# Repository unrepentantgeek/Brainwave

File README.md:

Description
===========
Brainwave is a low cost controller for Reprap 3D printers derived from the well known Sanguinololu. The primary design goal was lower cost, achieved by providing only the minimum required components for a single extruder printer.  It can be used to drive a cartesian or delta style printer.

Features:
- Small footprint: only 60mm x 79mm!
- 12V power input
- Micro USB connector
- All connectors at edge of board, vertical or right-angle connectors will fit..
- Atmel AT90USB646 microcontroller w/ USB bootloader
- 1, 2, 16 or 32x microstepping @ up to 800mA
- Dual Z-axis connectors
- Optional per channel current attenuation
- Heated bed support with separate power input (up to 24V @ 15A)
- Integrated heater/thermistor/stepper connector for E channel
- Fan control

Instructions
============
1. Build, buy or borrow a Brainwave
2. Install Arduino 1.0.2
3. install the brainwave arduino hardware bundle from
   [github.com/unrepentantgeek/brainwave-arduino](http://github.com/unrepentantgeek/brainwave-arduino)
   into the Arduino hardware directory.
4. Get Marlin. I am maintaining a branch of Marlin that will compile for
   brainwave at [github.com/unrepentantgeek/Marlin](http://github.com/unrepentantgeek/Marlin/tree/brainwave)
   Marlin HEAD has support, but it doesn't always compile cleanly for this
   board.

Hardware configuration
----------------------
1. Set micro-stepping selector jumpers (D1, D2) per channel.  Short both for 32x
   microstepping.  See table on back of board for other configurations.
   <b>Default: single-step.</b>
2. Set stepper current reference voltages.  I = V / 2.55
   <b>Default: 1V == 400mA.</b>

Software configuration
----------------------

Open Arduino, find the Marlin directory and open Marlin.ino. Select 'Brainwave'
from the Board menu. Find the Configuration.h file and change
DEFAULT_AXIS_STEPS_PER_UNIT to suit your printer (remember, 32x microsteps!)
Power on the Brainwave and connect the USB cable (note: the brainwave will not
power up off USB, you need the 12V supply.) Hold down the PROGRAM button and
press RESET, the STATUS led should pulse. Press the Upload button in Arduino.
After a reset the brainwave will show up as a CDC ACM serial device
(/dev/ttyACM[0..9] on Linux) and be ready to accept commands.

Brandon Bowman wrote up an excellent guide for getting the board working under
Windows and MacOS:
[fabbersuw.blogspot.com/2012/12/if-your-brainwaves-got-no-brains-or.html](http://fabbersuw.blogspot.com/2012/12/if-your-brainwaves-got-no-brains-or.html)

Known issues
------------
- It may take a couple of presses of the RESET button to get the firmware to
  come up after flashing.
- You may need a thermistor or similar 100k resistance present across the bed
  and extruder thermistor inputs. Otherwise Marlin may go into a deathloop and
  you'll never even see a serial device. Even if it doesn't fall on it's face it
  will only sit and complain about too high temp.
- Marlin may lose/gain steps on the X axis.  If so swap X and E to limit the
  impact.  This has not been observed with Sprinter.  The issue is being
  investigated.

Special thanks
--------------
Julie Atwood
Matt Westervelt
Frederik Hubinette
Silas Snider
Johann Rocholl
JP Sugarbroad
Austin Appleby
Richard DeLeon
Plamena Milusheva
Mark Ganter
Brandon Bowman

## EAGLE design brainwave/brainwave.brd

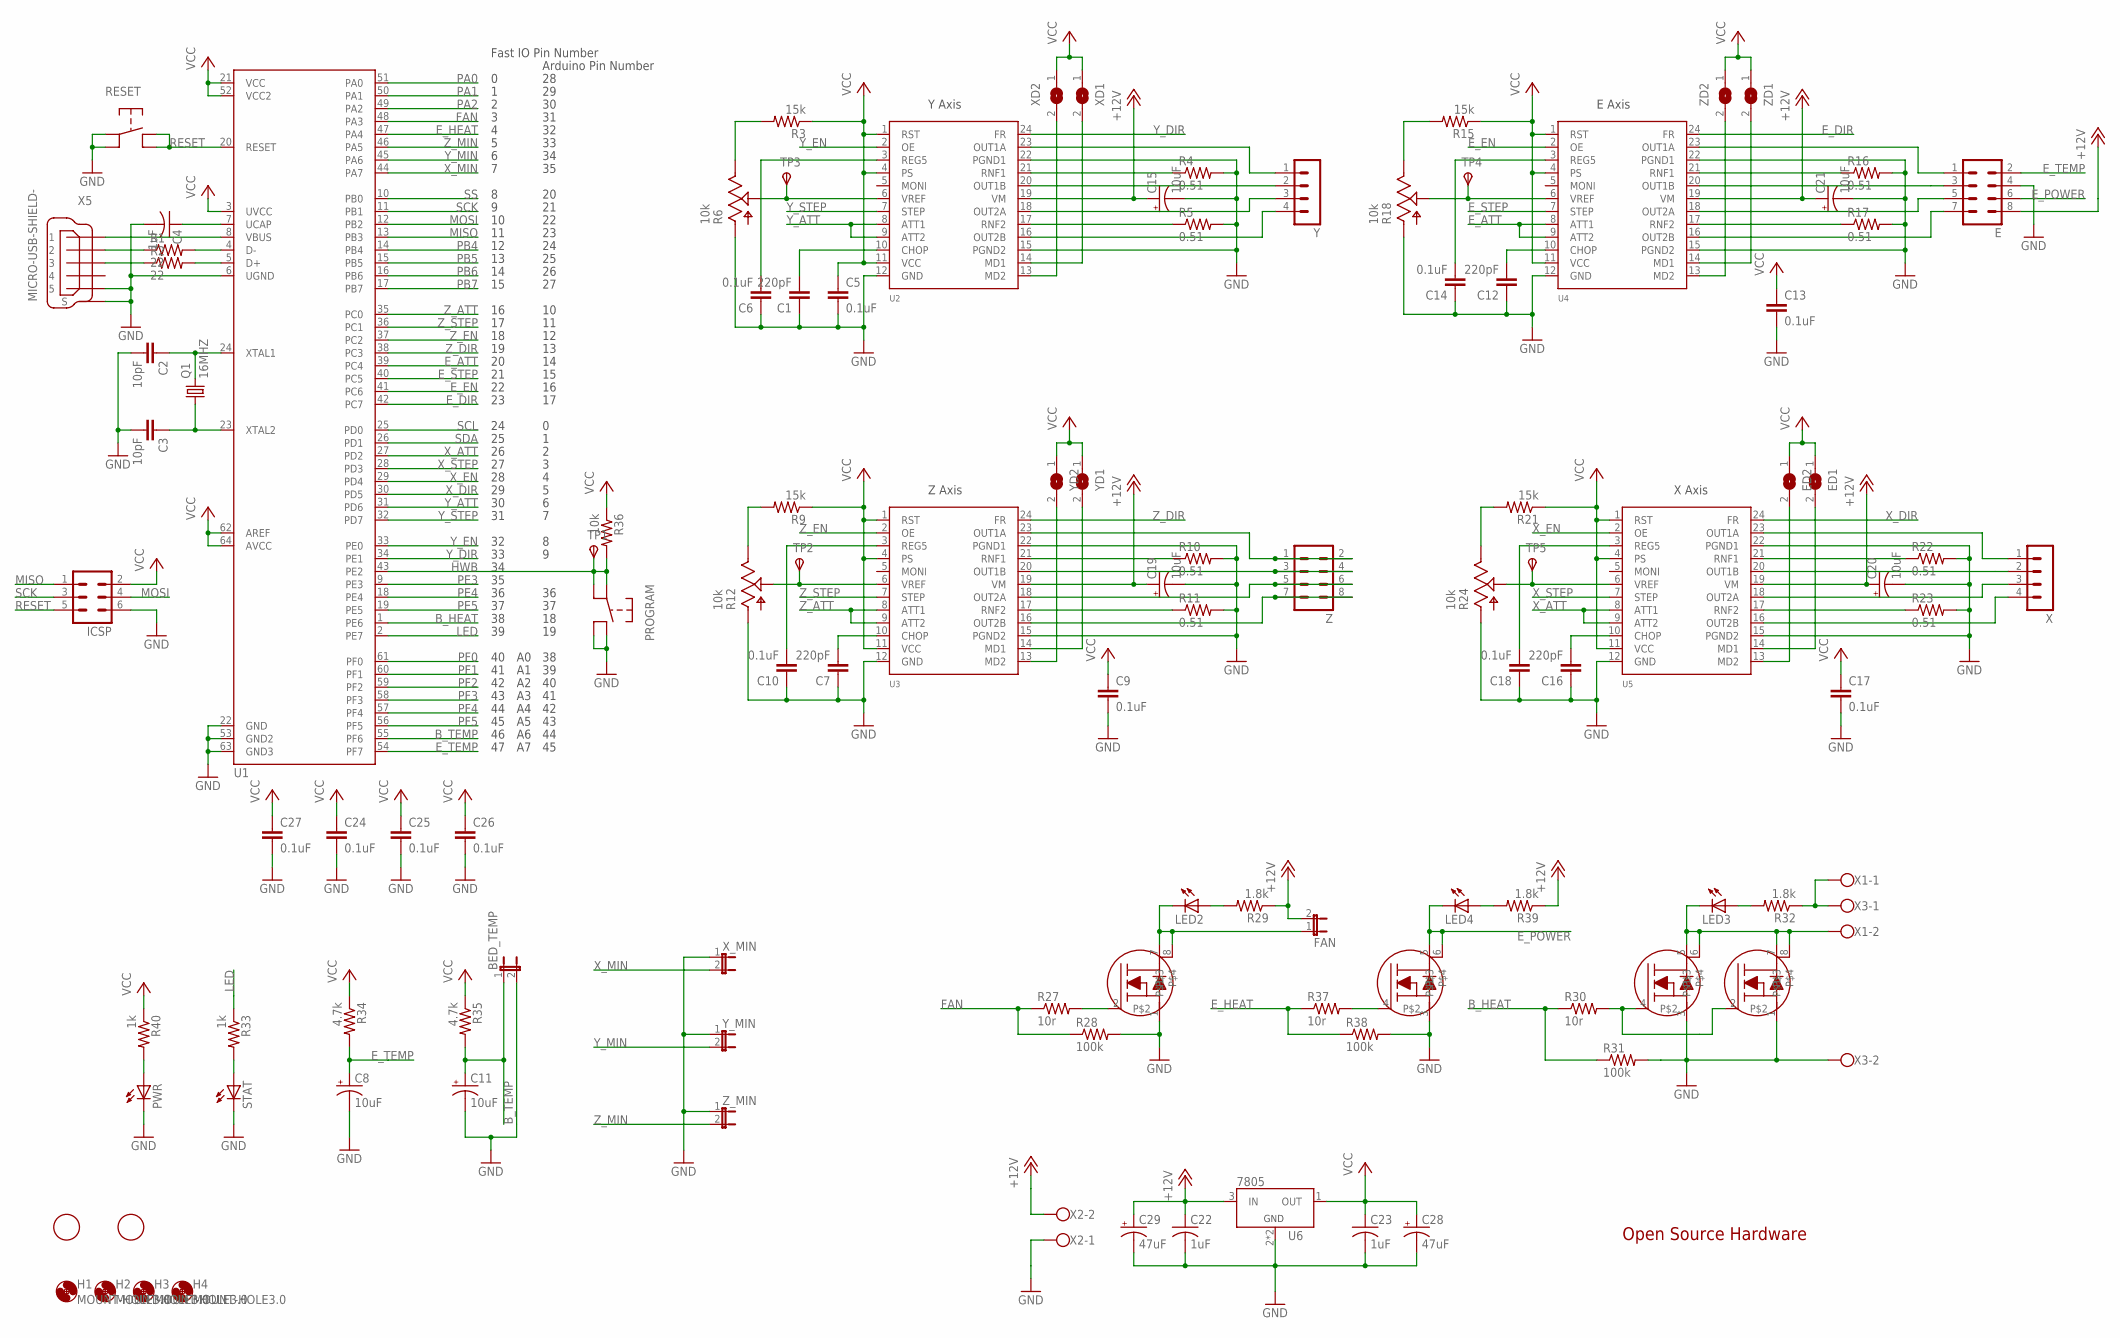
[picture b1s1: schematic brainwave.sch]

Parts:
BED_TEMP: JP1E; JP1
C1, C7, C12, C16: 220pF; C0603
C2, C3: 10pF; C0603
C4, C22, C23: 1uF; C0603
C5, C6, C9, C10, C13, C14, C17, C18, C24, C25, C26, C27: 0.1uF; C0603
C8, C11, C15, C19, C20, C21: 10uF; 153CLV-0505
C28, C29: 47uF; 153CLV-0605
E: MA04-2
ED1, ED2: SJ
FAN: JP1E; JP1
H1, H2, H3, H4: MOUNT-HOLE3.0; 3,0
ICSP: MA03-2
LED2, LED3, LED4: LEDCHIPLED_0805; CHIPLED_0805
PROGRAM: PTS645SMT; PTS645-SMTR
PWR: LEDCHIPLED_0805; CHIPLED_0805
Q1: 16MHZ; CSM-3X
R1, R2: 22; R0603
R3, R9, R15, R21: 15k; R0603
R4, R5, R10, R11, R16, R17, R22, R23: 0.51; R2512
R6, R12, R18, R24: 10k; PVZ3A
R27, R30, R37: 10r; R0603
R28, R31, R38: 100k; R0603
R29, R32, R39: 1.8k; R0603
R33, R40: 1k; R0603
R34, R35: 4.7k; R0603
R36: 10k; R0603
RESET: PTS645SMT; PTS645-SMTR
STAT: LEDCHIPLED_0805; CHIPLED_0805
TP1, TP2, TP3, TP4, TP5: TPSTP08R; TP08R
U1: AT90USB64/128; TQFP64
U2, U3, U4, U5: LV8713T; TSSOP24
U6: 7805; SOT89
U7, U8: IRF8313PBF; SO8
U$1, U$2: FIDUCIAL; FIDUCIAL_1MM
X: MA04-1
X1, X3: W237-102; MPN 237-102
X2: W237-102
X5: MICRO-USB-SHIELD-; 10118192-0001LF
XD1, XD2: SJ
X_MIN: JP1E; JP1
Y: MA04-1
YD1, YD2: SJ
Y_MIN: JP1E; JP1
Z: MA04-2
ZD1, ZD2: SJ
Z_MIN: JP1E; JP1

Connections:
+12V: C15.+, C19.+, C20.+, C21.+, C22.1, C29.+, E.8, FAN.2, R29.1, R39.1, U2.19 (VM), U3.19 (VM), U4.19 (VM), U5.19 (VM), U6.3 (IN), X2.2
BED_POWER: R32.1, X1.1, X3.1
B_HEAT: R30.1, R31.1, U1.1 (PE6)
B_TEMP: BED_TEMP.1, C11.+, R35.2, U1.55 (PF6)
E_ATT: U1.39 (PC4), U4.8 (ATT1), U4.9 (ATT2)
E_DIR: U1.42 (PC7), U4.24 (FR)
E_EN: U1.41 (PC6), U4.2 (OE)
E_HEAT: R37.1, R38.1, U1.47 (PA4)
E_POWER: E.6, LED4.C, U7.5, U7.6
E_STEP: U1.40 (PC5), U4.7 (STEP)
E_TEMP: C8.+, E.2, R34.2, U1.54 (PF7)
FAN: R27.1, R28.1, U1.48 (PA3)
GND: BED_TEMP.2, C1.1, C2.2, C3.2, C4.2, C5.2, C6.1, C7.1, C8.-, C9.2, C10.1, C11.-, C12.1, C13.2, C14.1, C15.-, C16.1, C17.2, C18.1, C19.-, C20.-, C21.-, C22.2, C23.2, C24.2, C25.2, C26.2, C27.2, C28.-, C29.-, E.4, ICSP.6, PROGRAM.P$3, PROGRAM.P$4, PWR.C, R4.2, R5.2, R6.P$1, R10.2, R11.2, R12.P$1, R16.2, R17.2, R18.P$1, R22.2, R23.2, R24.P$1, R28.2, R31.2, R38.2, RESET.P$1, RESET.P$2, STAT.C, U1.6 (UGND), U1.22 (GND), U1.53 (GND2), U1.63 (GND3), U2.12 (GND), U2.15 (PGND2), U2.22 (PGND1), U3.12 (GND), U3.15 (PGND2), U3.22 (PGND1), U4.12 (GND), U4.15 (PGND2), U4.22 (PGND1), U5.12 (GND), U5.15 (PGND2), U5.22 (PGND1), U6.2 (GND), U6.2@1 (GND), U7.1, U7.3, U8.1, U8.3, X2.1, X3.2, X5.5, X5.M1 (S), X5.M2 (S), X5.M3 (S), X5.M4 (S), X5.M5 (S), X5.M6 (S), X_MIN.1, Y_MIN.1, Z_MIN.1
HWB: PROGRAM.P$1, PROGRAM.P$2, R36.2, TP1.TP, U1.43 (PE2)
LED: R33.1, U1.2 (PE7)
MISO: ICSP.1, U1.13 (PB3)
MOSI: ICSP.4, U1.12 (PB2)
unnamed: U1.8 (VBUS), X5.1
unnamed: R1.1, X5.2
unnamed: R2.1, X5.3
unnamed: U3.20 (OUT1B), Z.3, Z.4
unnamed: C4.1, U1.7 (UCAP)
unnamed: C2.1, Q1.2, U1.24 (XTAL1)
unnamed: C3.1, Q1.1, U1.23 (XTAL2)
unnamed: R6.P$2, TP3.TP, U2.6 (VREF)
unnamed: R4.1, U2.21 (RNF1)
unnamed: R5.1, U2.17 (RNF2)
unnamed: U2.16 (OUT2B), Y.4
unnamed: U2.18 (OUT2A), Y.3
unnamed: U2.20 (OUT1B), Y.2
unnamed: U2.23 (OUT1A), Y.1
unnamed: C1.2, U2.10 (CHOP)
unnamed: C6.2, U2.3 (REG5)
unnamed: R3.2, R6.P$3
unnamed: U2.13 (MD2), XD2.2
unnamed: U2.14 (MD1), XD1.2
unnamed: R30.2, U8.2, U8.4
unnamed: R10.1, U3.21 (RNF1)
unnamed: R11.1, U3.17 (RNF2)
unnamed: U3.16 (OUT2B), Z.7, Z.8
unnamed: U3.18 (OUT2A), Z.5, Z.6
unnamed: U3.23 (OUT1A), Z.1, Z.2
unnamed: C7.2, U3.10 (CHOP)
unnamed: C10.2, U3.3 (REG5)
unnamed: R12.P$2, TP2.TP, U3.6 (VREF)
unnamed: R9.2, R12.P$3
unnamed: U3.13 (MD2), YD2.2
unnamed: U3.14 (MD1), YD1.2
unnamed: R33.2, STAT.A
unnamed: R37.2, U7.4
unnamed: LED4.A, R39.2
unnamed: PWR.A, R40.2
unnamed: R16.1, U4.21 (RNF1)
unnamed: R17.1, U4.17 (RNF2)
unnamed: E.7, U4.16 (OUT2B)
unnamed: E.5, U4.18 (OUT2A)
unnamed: E.3, U4.20 (OUT1B)
unnamed: E.1, U4.23 (OUT1A)
unnamed: C12.2, U4.10 (CHOP)
unnamed: C14.2, U4.3 (REG5)
unnamed: R18.P$2, TP4.TP, U4.6 (VREF)
unnamed: R15.2, R18.P$3
unnamed: U4.13 (MD2), ZD2.2
unnamed: U4.14 (MD1), ZD1.2
unnamed: R22.1, U5.21 (RNF1)
unnamed: R23.1, U5.17 (RNF2)
unnamed: U5.16 (OUT2B), X.4
unnamed: U5.18 (OUT2A), X.3
unnamed: U5.20 (OUT1B), X.2
unnamed: U5.23 (OUT1A), X.1
unnamed: C16.2, U5.10 (CHOP)
unnamed: C18.2, U5.3 (REG5)
unnamed: R24.P$2, TP5.TP, U5.6 (VREF)
unnamed: R21.2, R24.P$3
unnamed: ED2.2, U5.13 (MD2)
unnamed: ED1.2, U5.14 (MD1)
unnamed: R27.2, U7.2
unnamed: LED2.A, R29.2
unnamed: FAN.1, LED2.C, U7.7, U7.8
unnamed: LED3.C, U8.5, U8.6, U8.7, U8.8, X1.2
unnamed: LED3.A, R32.2
PA0: U1.51 (PA0)
PA1: U1.50 (PA1)
PA2: U1.49 (PA2)
PB4: U1.14 (PB4)
PB5: U1.15 (PB5)
PB6: U1.16 (PB6)
PB7: U1.17 (PB7)
PE3: U1.9 (PE3)
PE4: U1.18 (PE4)
PE5: U1.19 (PE5)
PF0: U1.61 (PF0)
PF1: U1.60 (PF1)
PF2: U1.59 (PF2)
PF3: U1.58 (PF3)
PF4: U1.57 (PF4)
PF5: U1.56 (PF5)
RESET: ICSP.5, RESET.P$3, RESET.P$4, U1.20 (RESET)
SCK: ICSP.3, U1.11 (PB1)
SCL: U1.25 (PD0)
SDA: U1.26 (PD1)
SS: U1.10 (PB0)
USB1_N: R1.2, U1.4 (D-)
USB1_P: R2.2, U1.5 (D+)
VCC: C5.1, C9.1, C13.1, C17.1, C23.1, C24.1, C25.1, C26.1, C27.1, C28.+, ED1.1, ED2.1, ICSP.2, R3.1, R9.1, R15.1, R21.1, R34.1, R35.1, R36.1, R40.1, U1.3 (UVCC), U1.21 (VCC), U1.52 (VCC2), U1.62 (AREF), U1.64 (AVCC), U2.1 (RST), U2.4 (PS), U2.11 (VCC), U3.1 (RST), U3.4 (PS), U3.11 (VCC), U4.1 (RST), U4.4 (PS), U4.11 (VCC), U5.1 (RST), U5.4 (PS), U5.11 (VCC), U6.1 (OUT), XD1.1, XD2.1, YD1.1, YD2.1, ZD1.1, ZD2.1
X_ATT: U1.27 (PD2), U5.8 (ATT1), U5.9 (ATT2)
X_DIR: U1.30 (PD5), U5.24 (FR)
X_EN: U1.29 (PD4), U5.2 (OE)
X_MIN: U1.44 (PA7), X_MIN.2
X_STEP: U1.28 (PD3), U5.7 (STEP)
Y_ATT: U1.31 (PD6), U2.8 (ATT1), U2.9 (ATT2)
Y_DIR: U1.34 (PE1), U2.24 (FR)
Y_EN: U1.33 (PE0), U2.2 (OE)
Y_MIN: U1.45 (PA6), Y_MIN.2
Y_STEP: U1.32 (PD7), U2.7 (STEP)
Z_ATT: U1.35 (PC0), U3.8 (ATT1), U3.9 (ATT2)
Z_DIR: U1.38 (PC3), U3.24 (FR)
Z_EN: U1.37 (PC2), U3.2 (OE)
Z_MIN: U1.46 (PA5), Z_MIN.2
Z_STEP: U1.36 (PC1), U3.7 (STEP)

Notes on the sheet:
E Axis
Z Axis
X Axis
Y Axis
Fast IO Pin Number
Open Source Hardware
Arduino Pin Number

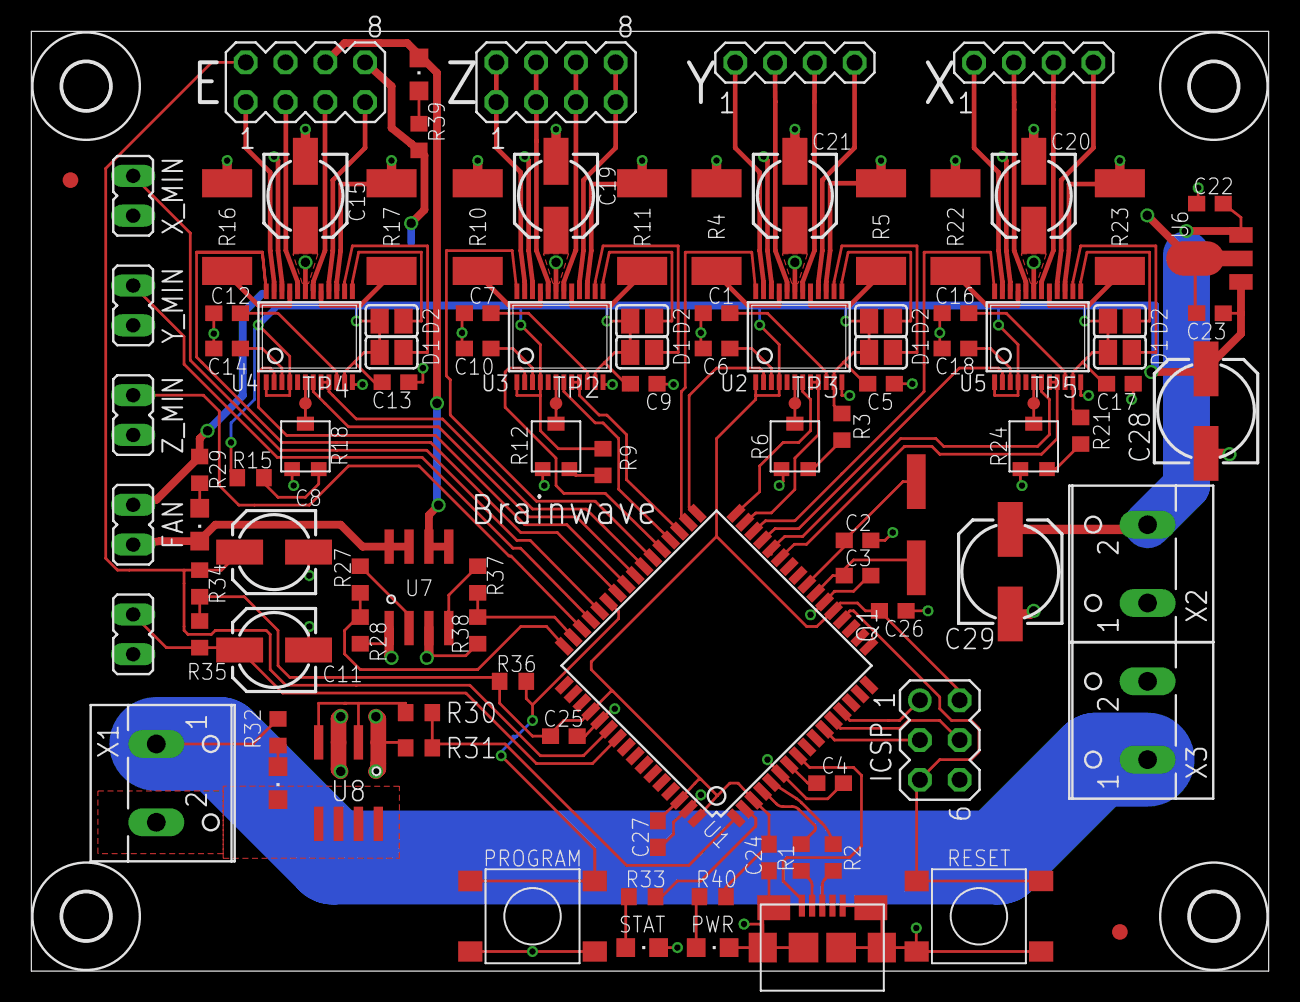
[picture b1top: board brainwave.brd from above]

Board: 2 copper layers, 79.0 x 60.0 mm, 110 parts (1 on the bottom side), 101 nets.

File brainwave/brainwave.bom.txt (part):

Part     Value             Device             Package         Description                                                            
BED_TEMP                   JP1E               JP1             JUMPER                                                                 
C1       220pF             C-EUC0603          C0603           CAPACITOR, European symbol                                             
C2       10pF              C-EUC0603          C0603           CAPACITOR, European symbol                                             
C3       10pF              C-EUC0603          C0603           CAPACITOR, European symbol                                             
C4       1uF               C-USC0603          C0603           CAPACITOR, American symbol                                             
C5       0.1uF             C-EUC0603          C0603           CAPACITOR, European symbol                                             
C6       0.1uF             C-EUC0603          C0603           CAPACITOR, European symbol                                             
C7       220pF             C-EUC0603          C0603           CAPACITOR, European symbol                                             
C8       10uF              CPOL-US153CLV-0505 153CLV-0505     POLARIZED CAPACITOR, American symbol                                   
C9       0.1uF             C-EUC0603          C0603           CAPACITOR, European symbol                                             
C10      0.1uF             C-EUC0603          C0603           CAPACITOR, European symbol                                             
C11      10uF              CPOL-US153CLV-0505 153CLV-0505     POLARIZED CAPACITOR, American symbol                                   
C12      220pF             C-EUC0603          C0603           CAPACITOR, European symbol                                             
C13      0.1uF             C-EUC0603          C0603           CAPACITOR, European symbol                                             
C14      0.1uF             C-EUC0603          C0603           CAPACITOR, European symbol                                             
C15      10uF              CPOL-US153CLV-0505 153CLV-0505     POLARIZED CAPACITOR, American symbol                                   
C16      220pF             C-EUC0603          C0603           CAPACITOR, European symbol                                             
C17      0.1uF             C-EUC0603          C0603           CAPACITOR, European symbol                                             
C18      0.1uF             C-EUC0603          C0603           CAPACITOR, European symbol                                             
C19      10uF              CPOL-US153CLV-0505 153CLV-0505     POLARIZED CAPACITOR, American symbol                                   
C20      10uF              CPOL-US153CLV-0505 153CLV-0505     POLARIZED CAPACITOR, American symbol                                   
C21      10uF              CPOL-US153CLV-0505 153CLV-0505     POLARIZED CAPACITOR, American symbol                                   
C22      1uF               C-USC0603          C0603           CAPACITOR, American symbol                                             
C23      1uF               C-USC0603          C0603           CAPACITOR, American symbol                                             
C24      0.1uF             C-EUC0603          C0603           CAPACITOR, European symbol                                             
C25      0.1uF             C-EUC0603          C0603           CAPACITOR, European symbol                                             
C26      0.1uF             C-EUC0603          C0603           CAPACITOR, European symbol                                             
C27      0.1uF             C-EUC0603          C0603           CAPACITOR, European symbol                                             
C28      47uF              CPOL-US153CLV-0605 153CLV-0605     POLARIZED CAPACITOR, American symbol                                   
C29      47uF              CPOL-US153CLV-0605 153CLV-0605     POLARIZED CAPACITOR, American symbol                                   
E                          MA04-2             MA04-2          PIN HEADER                                                             
FAN                        JP1E               JP1             JUMPER                                                                 
ICSP                       MA03-2             MA03-2          PIN HEADER                                                             
LED2                       LEDCHIPLED_0805    CHIPLED_0805    LED                                                                    
LED3                       LEDCHIPLED_0805    CHIPLED_0805    LED                                                                    
LED4                       LEDCHIPLED_0805    CHIPLED_0805    LED                                                                    
PROGRAM  PTS645SMT         PTS645SMT          PTS645-SMTR                                                                            
PWR                        LEDCHIPLED_0805    CHIPLED_0805    LED                                                                    
Q1       16MHZ             CRYSTALCSM-3X      CSM-3X          SMD CRYSTAL                                                            
R1       22                R-US_R0603         R0603           RESISTOR, American symbol                                              
R2       22                R-US_R0603         R0603           RESISTOR, American symbol                                              
R3       15k               R-US_R0603         R0603           RESISTOR, American symbol                                              
R4       0.51              R-US_R2512         R2512           RESISTOR, American symbol                                              
R5       0.51              R-US_R2512         R2512           RESISTOR, American symbol                                              
R6       10k               PVZ3A              PVZ3A                                                                                  
R9       15k               R-US_R0603         R0603           RESISTOR, American symbol                                              
R10      0.51              R-US_R2512         R2512           RESISTOR, American symbol                                              
R11      0.51              R-US_R2512         R2512           RESISTOR, American symbol                                              
R12      10k               PVZ3A              PVZ3A                                                                                  
R15      15k               R-US_R0603         R0603           RESISTOR, American symbol                                              
R16      0.51              R-US_R2512         R2512           RESISTOR, American symbol                                              
R17      0.51              R-US_R2512         R2512           RESISTOR, American symbol                                              
R18      10k               PVZ3A              PVZ3A                                                                                  
R21      15k               R-US_R0603         R0603           RESISTOR, American symbol                                              
R22      0.51              R-US_R2512         R2512           RESISTOR, American symbol                                              
R23      0.51              R-US_R2512         R2512           RESISTOR, American symbol                                              
R24      10k               PVZ3A              PVZ3A                                                                                  
R27      10r               R-US_R0603         R0603           RESISTOR, American symbol                                              
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
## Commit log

2012-12-11 Version 1.0 final schematic and board files
2013-02-03 Update readme add BOM put license in silk

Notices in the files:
brainwave/brainwave.brd:
GPL 2.0
